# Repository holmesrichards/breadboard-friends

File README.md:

breadboard-friends
==================

A collection of cute breakout boards riding solderless breadboards, mostly for analog audio works

Forked from pichenettes' version and identical except:
- Eagle brd and sch files converted to XML (making possible import into KiCad)
- KiCad versions of boards and schematics
- Added Thonkiconn version of eurojacks

These PCB layouts and schematics are released under a Creative Commons cc-by-sa
3.0 license.

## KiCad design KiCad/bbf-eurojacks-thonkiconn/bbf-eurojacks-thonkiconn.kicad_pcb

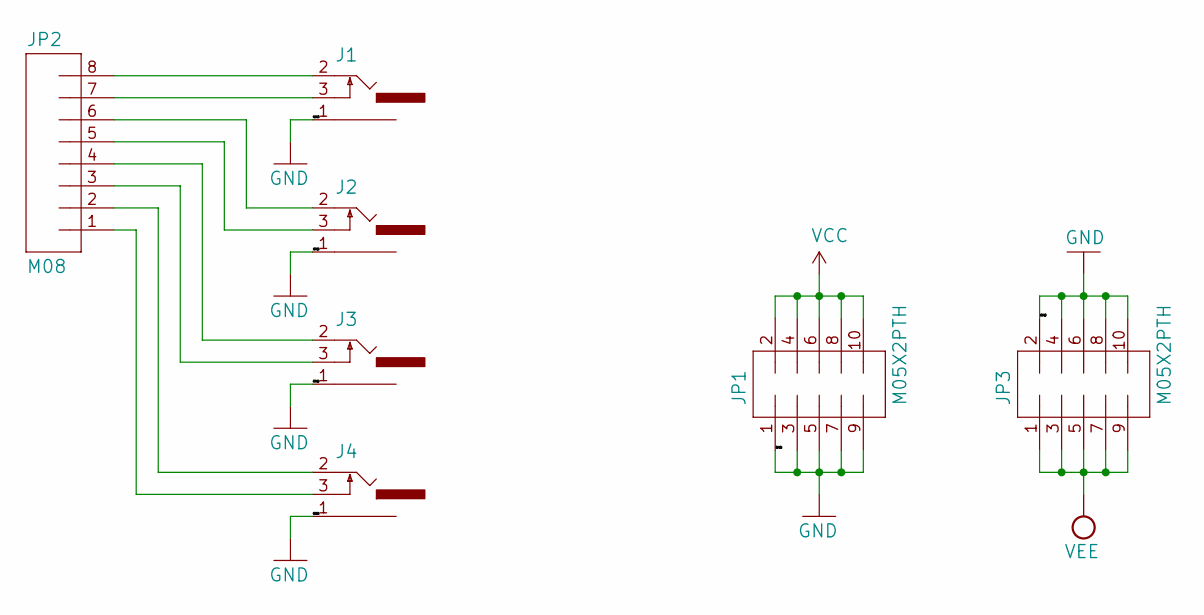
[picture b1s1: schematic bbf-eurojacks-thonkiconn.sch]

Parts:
J1, J2, J3, J4: 1502_03SLOTTED; 3.5mm_tip_switch_thonkiconn
JP1, JP3: M05X2PTH; AVR_ICSP
JP2: M08; 1X08

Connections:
GND: J1.1, J2.1, J3.1, J4.1, JP1.1, JP1.3, JP1.5, JP1.7, JP1.9, JP3.2, JP3.4, JP3.6, JP3.8, JP3.10
unnamed: J1.2, JP2.8
unnamed: J1.3, JP2.7
unnamed: J2.2, JP2.6
unnamed: J2.3, JP2.5
unnamed: J3.2, JP2.4
unnamed: J3.3, JP2.3
unnamed: J4.2, JP2.2
unnamed: J4.3, JP2.1
VCC: JP1.2, JP1.4, JP1.6, JP1.8, JP1.10
VEE: JP3.1, JP3.3, JP3.5, JP3.7, JP3.9

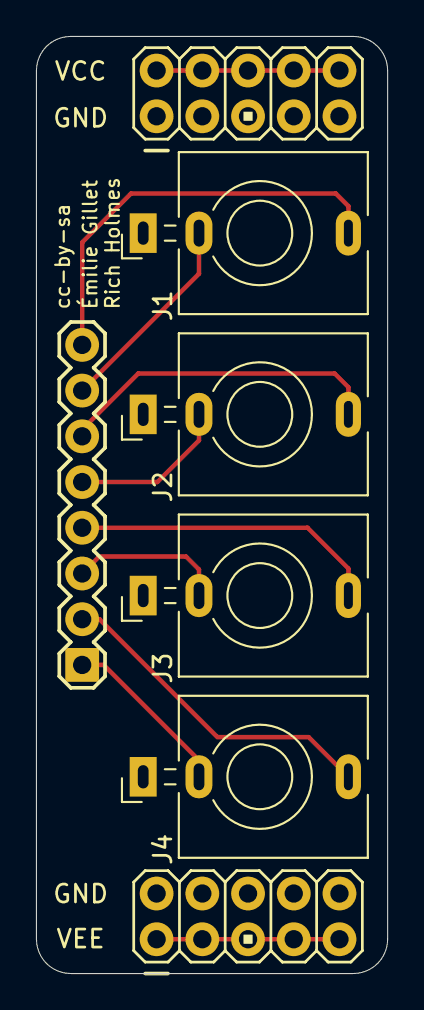
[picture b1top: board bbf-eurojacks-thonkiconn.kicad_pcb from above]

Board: 2 copper layers, 19.5 x 52.1 mm, 7 parts (0 on the bottom side), 11 nets.

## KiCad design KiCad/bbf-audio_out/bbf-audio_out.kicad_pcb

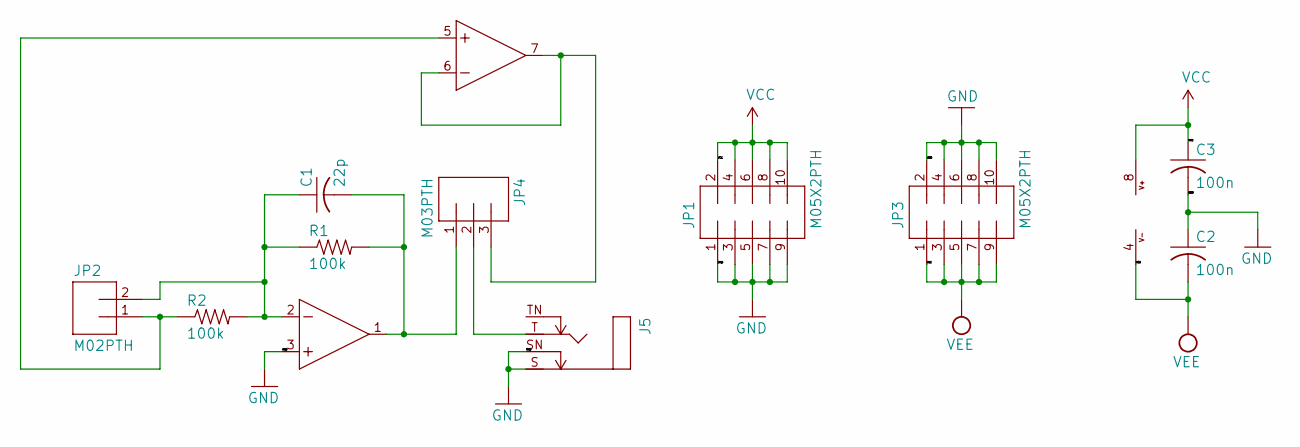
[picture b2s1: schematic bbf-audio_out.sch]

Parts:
C1: 22p; C025-025X050
C2, C3: 100n; C025-025X050
IC1: TL072P; DIL08
J5: MONOSWSLIM; NRJ4HF
JP1, JP3: M05X2PTH; AVR_ICSP
JP2: M02PTH; 1X02
JP4: M03PTH; 1X03
R1, R2: 100k; 0204_7

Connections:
GND: C2.1, C3.2, IC1.3 (+IN), J5.S, J5.SN, JP1.1, JP1.3, JP1.5, JP1.7, JP1.9, JP3.2, JP3.4, JP3.6, JP3.8, JP3.10
unnamed: C1.1, IC1.2 (-IN), JP2.2, R1.1, R2.2
unnamed: C1.2, IC1.1 (OUT), JP4.1, R1.2
unnamed: IC1.5 (+IN), JP2.1, R2.1
unnamed: IC1.6 (-IN), IC1.7 (OUT), JP4.3
unnamed: J5.T, JP4.2
VCC: C3.1, IC1.8 (V+), JP1.2, JP1.4, JP1.6, JP1.8, JP1.10
VEE: C2.2, IC1.4 (V-), JP3.1, JP3.3, JP3.5, JP3.7, JP3.9

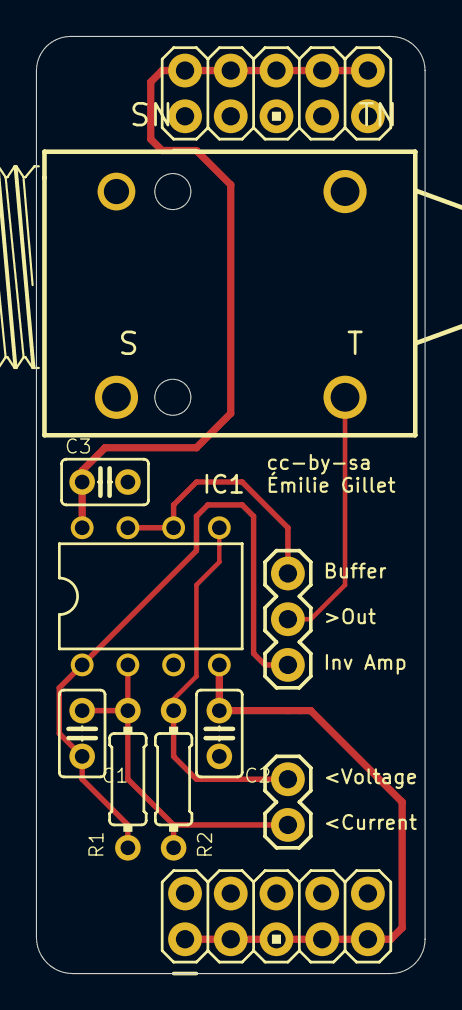
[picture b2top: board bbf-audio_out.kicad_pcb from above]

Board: 2 copper layers, 21.6 x 52.1 mm, 11 parts (0 on the bottom side), 8 nets.

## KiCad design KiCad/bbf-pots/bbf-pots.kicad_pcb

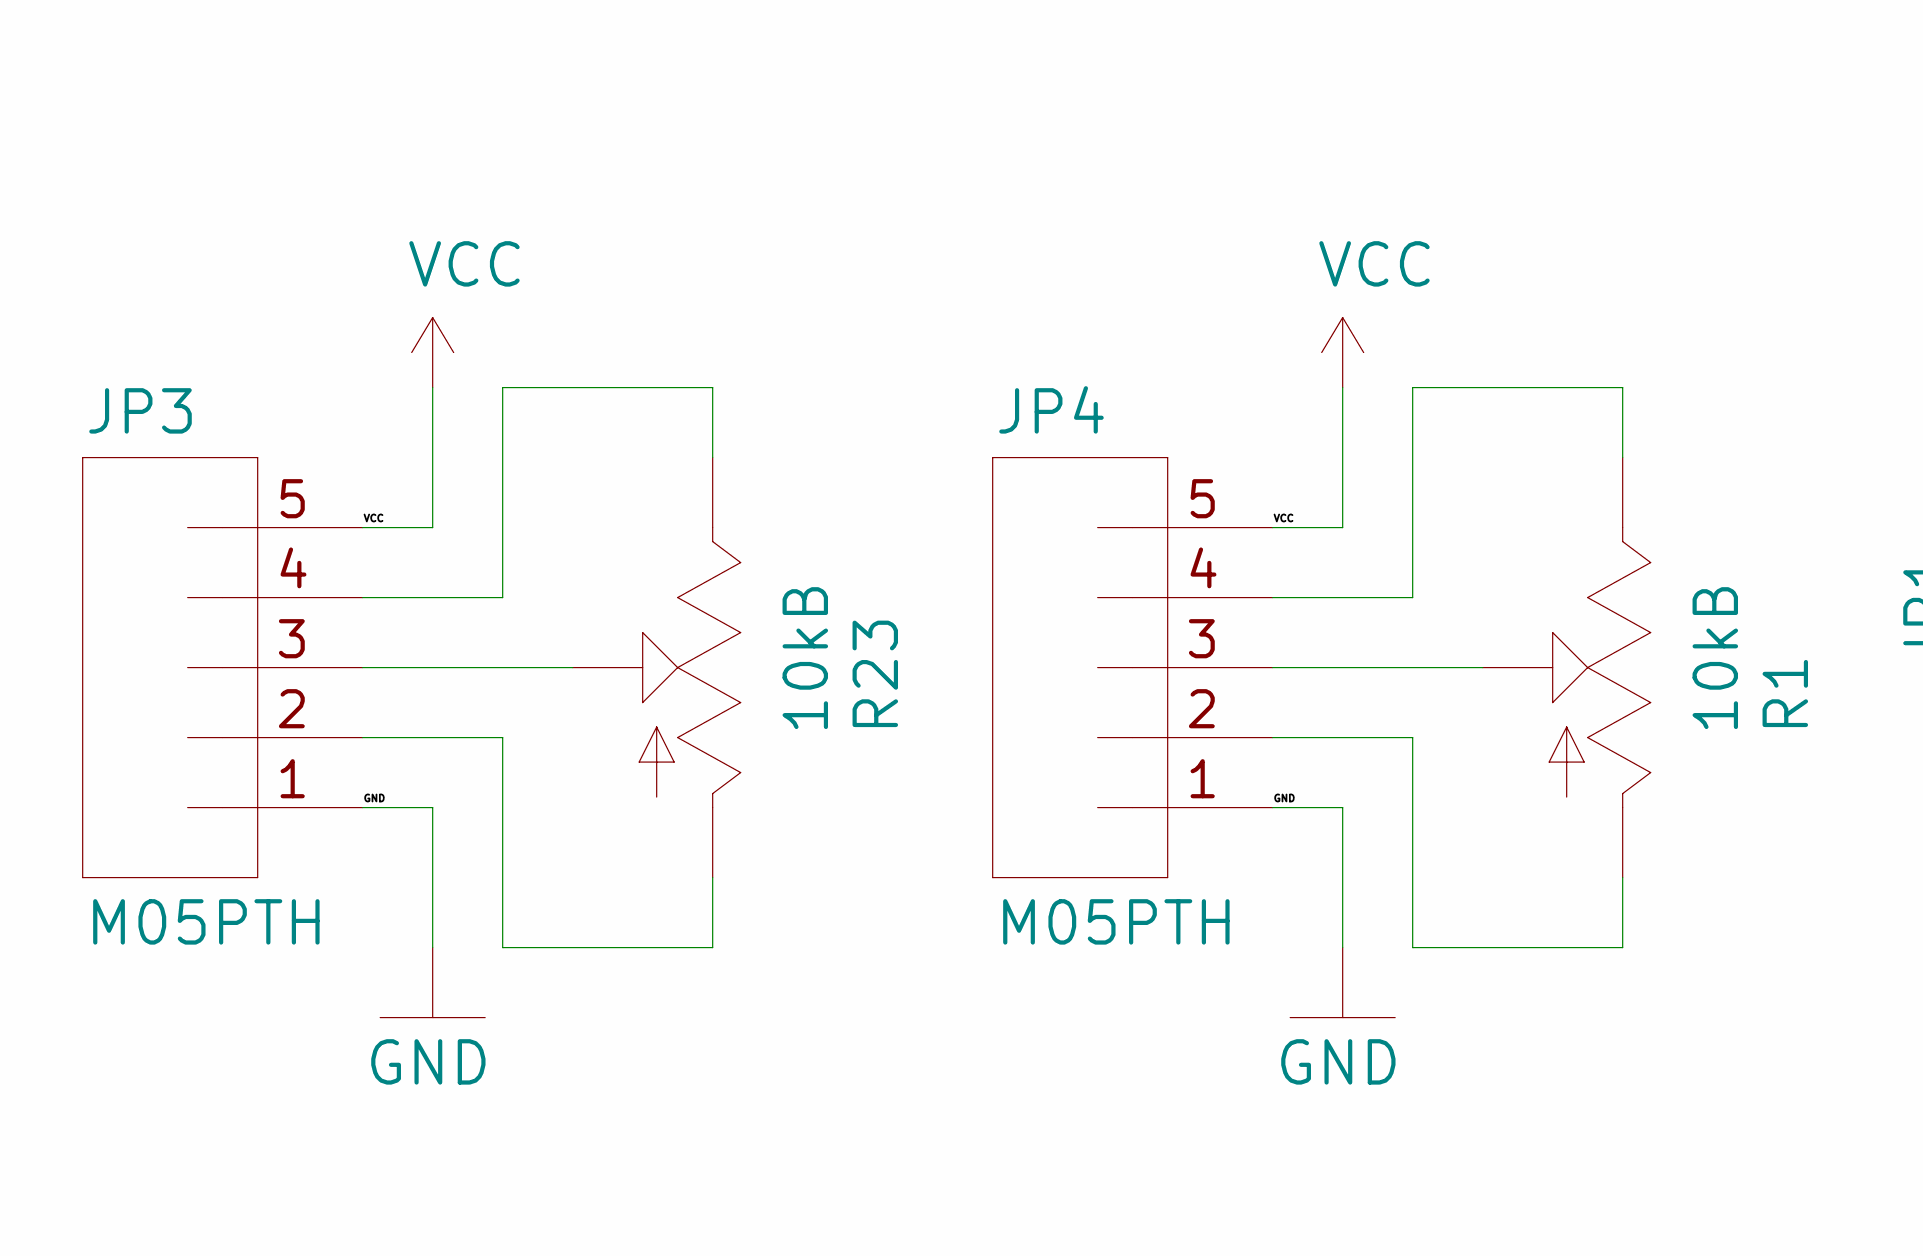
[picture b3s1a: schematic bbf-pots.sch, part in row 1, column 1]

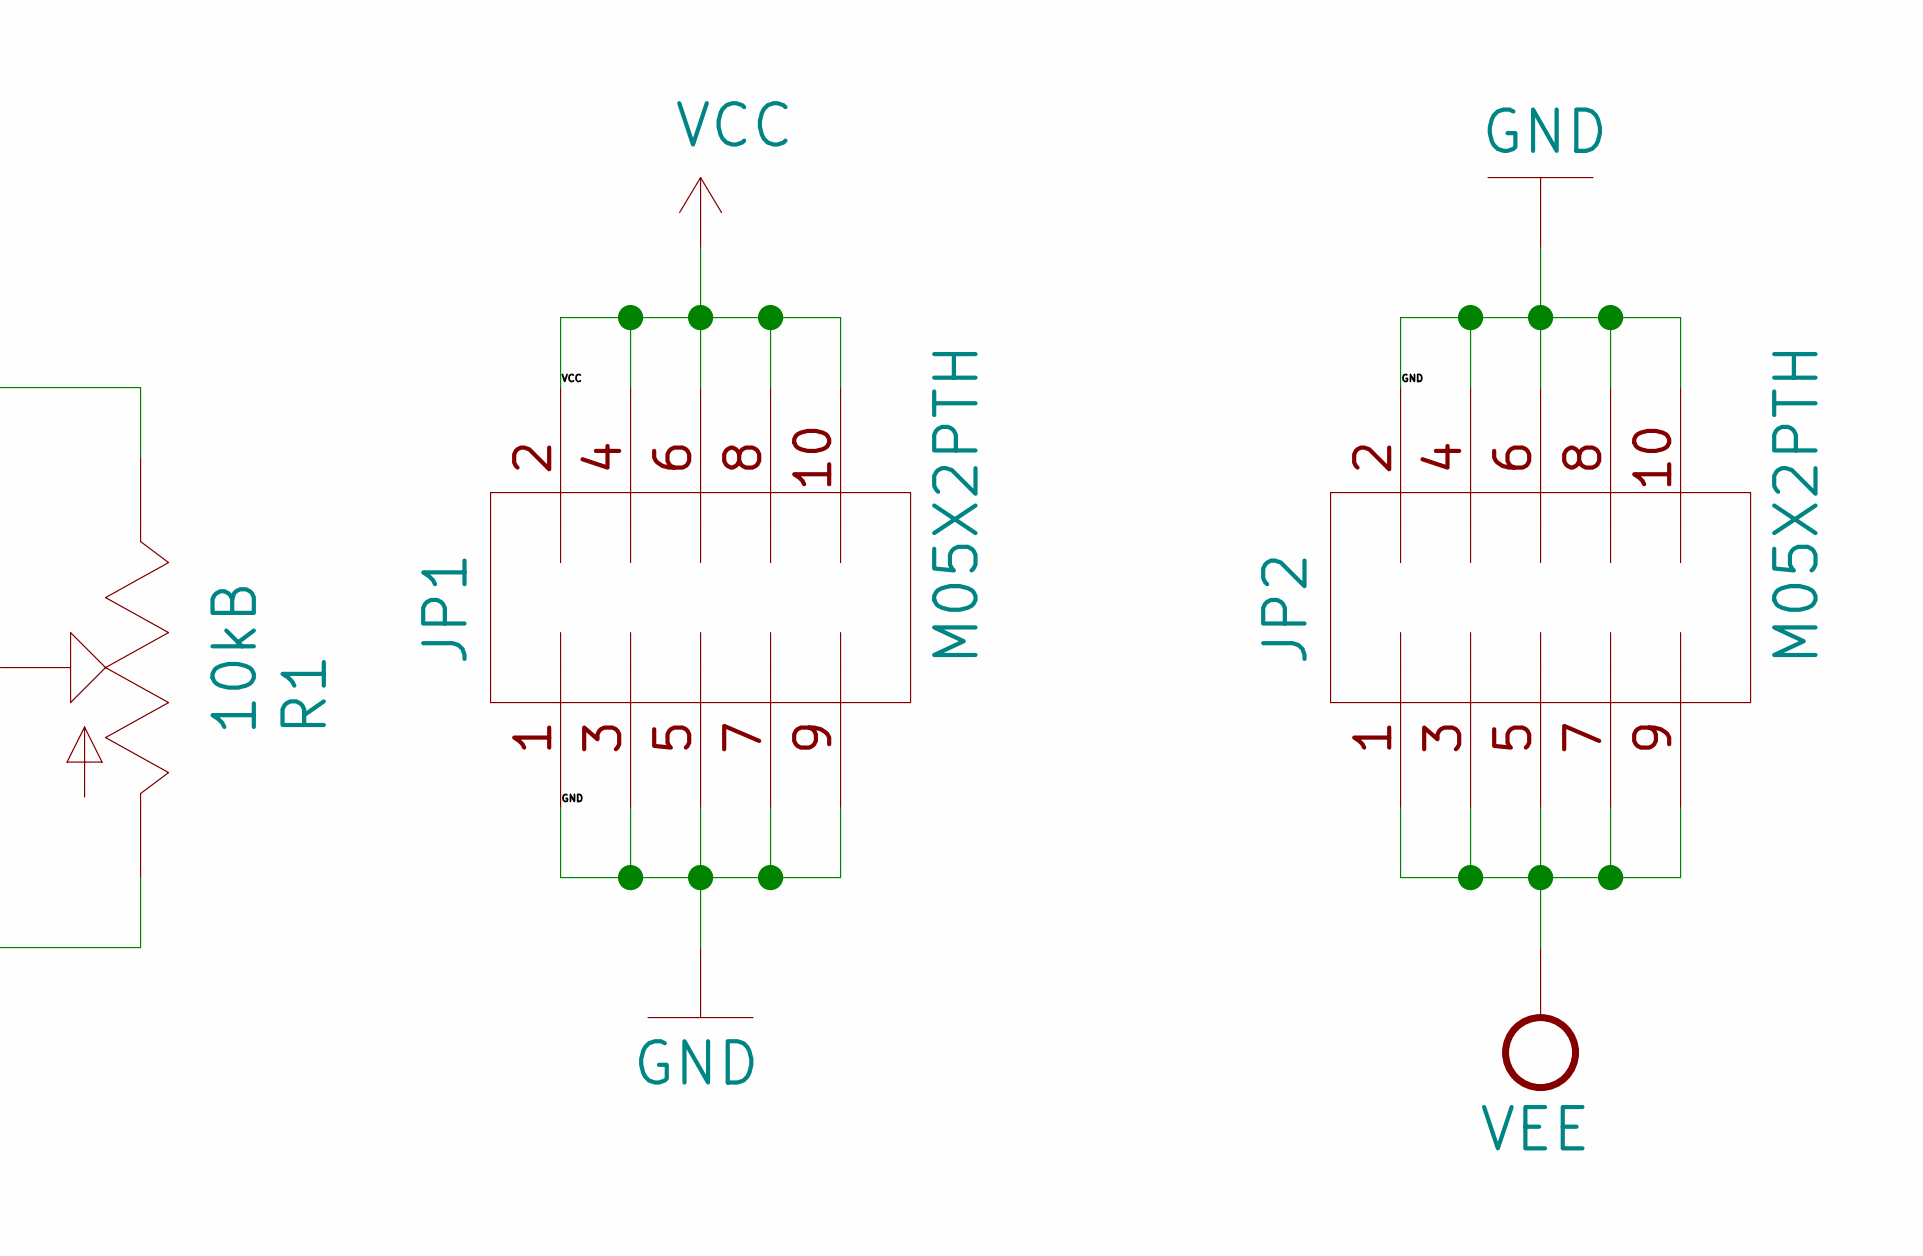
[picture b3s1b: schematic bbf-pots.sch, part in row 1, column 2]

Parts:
JP1, JP2: M05X2PTH; AVR_ICSP
JP3, JP4: M05PTH; 1X05
R1, R23: 10kB; ALPS_POT_VERTICAL

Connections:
GND: JP1.1, JP1.3, JP1.5, JP1.7, JP1.9, JP2.2, JP2.4, JP2.6, JP2.8, JP2.10, JP3.1, JP4.1
unnamed: JP3.2, R23.P$3 (A)
unnamed: JP3.3, R23.P$2 (S)
unnamed: JP3.4, R23.P$1 (E)
unnamed: JP4.2, R1.P$3 (A)
unnamed: JP4.3, R1.P$2 (S)
unnamed: JP4.4, R1.P$1 (E)
VCC: JP1.2, JP1.4, JP1.6, JP1.8, JP1.10, JP3.5, JP4.5
VEE: JP2.1, JP2.3, JP2.5, JP2.7, JP2.9

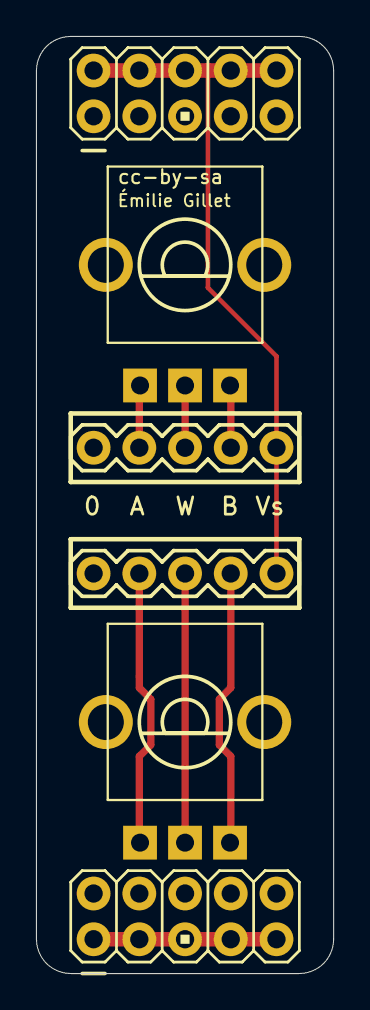
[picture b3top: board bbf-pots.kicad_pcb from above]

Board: 2 copper layers, 16.5 x 52.1 mm, 6 parts (0 on the bottom side), 9 nets.

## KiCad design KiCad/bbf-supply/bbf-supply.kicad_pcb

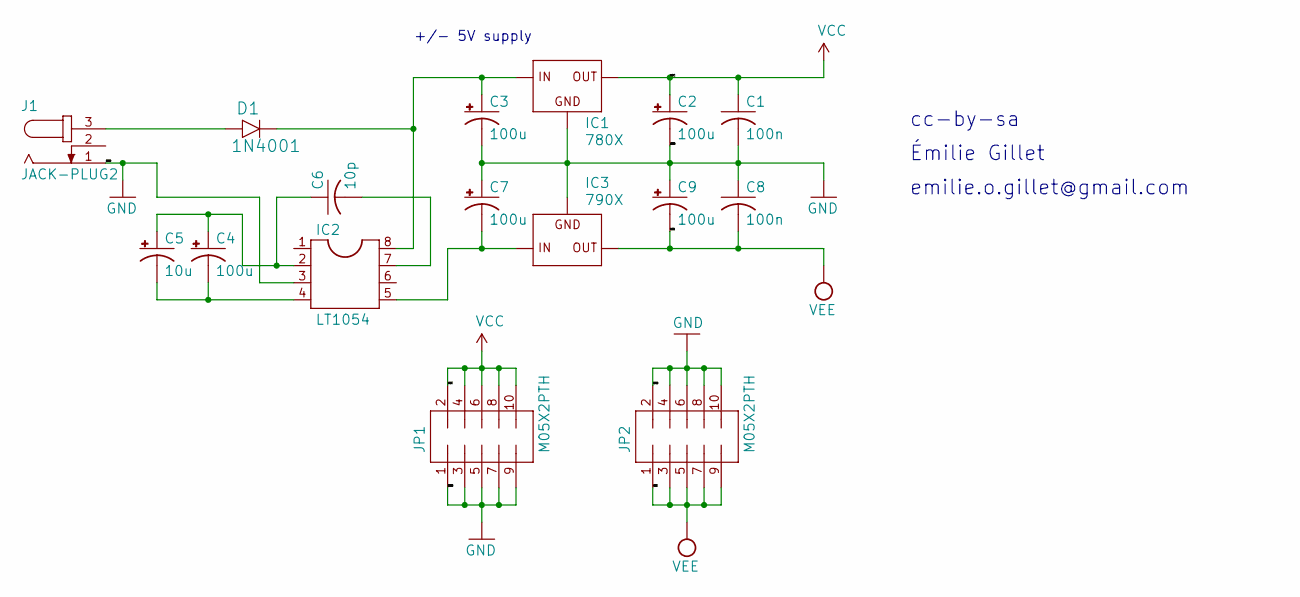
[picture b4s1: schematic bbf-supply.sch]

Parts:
C1, C8: 100n; C025-025X050
C2, C3, C7, C9: 100u; E2,5-7
C4: 100u; E2,5-6
C5: 10u; E2,5-5
C6: 10p; C025-025X050
D1: 1N4001; DO41-3
IC1: 780X; 78XXS
IC2: LT1054; DIL08
IC3: 790X; 79XXS
J1: JACK-PLUG2; SPC4078_BIG_HOLES
JP1, JP2: M05X2PTH; AVR_ICSP

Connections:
GND: C1.2, C2.-, C3.-, C7.+, C8.1, C9.+, IC1.GND, IC2.3, IC3.GND, J1.1, JP1.1, JP1.3, JP1.5, JP1.7, JP1.9, JP2.2, JP2.4, JP2.6, JP2.8, JP2.10
unnamed: C3.+, D1.C, IC1.IN, IC2.8
unnamed: C4.+, C5.+, C6.1, IC2.2
unnamed: C4.-, C5.-, IC2.4
unnamed: C6.2, IC2.7
unnamed: C7.-, IC2.5, IC3.IN
unnamed: D1.A, J1.3
VCC: C1.1, C2.+, IC1.OUT, JP1.2, JP1.4, JP1.6, JP1.8, JP1.10
VEE: C8.2, C9.-, IC3.OUT, JP2.1, JP2.3, JP2.5, JP2.7, JP2.9

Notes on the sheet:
cc-by-sa
Émilie Gillet
emilie.o.gillet@gmail.com
+/- 5V supply

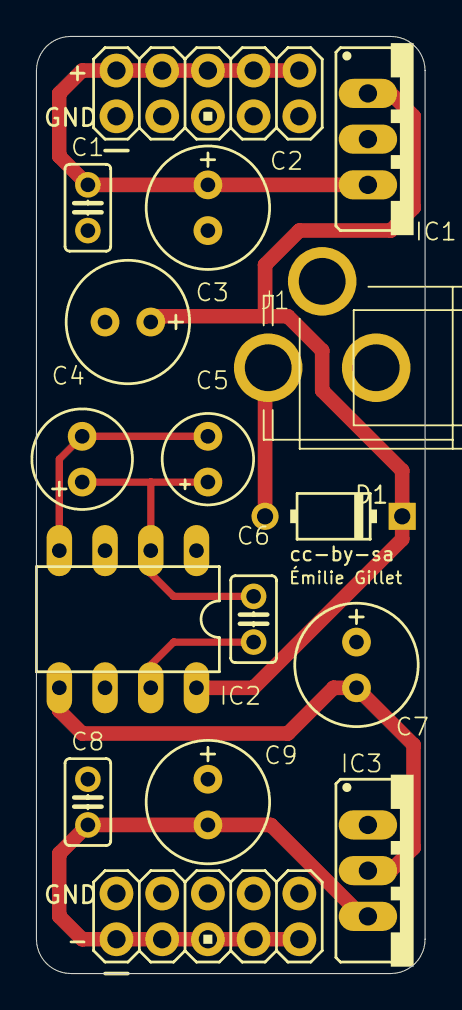
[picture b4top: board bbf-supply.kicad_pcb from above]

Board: 2 copper layers, 21.6 x 52.1 mm, 16 parts (0 on the bottom side), 9 nets.

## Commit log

2020-03-22 add KiCad stuff
2020-03-22 XML conversions
2020-03-22 KiCad conversions and (KiCad) Thonkiconn version of eurojacks
2020-03-22 lose KiCad cruft
2020-03-23 Updated README for fork
2020-03-23 euroracks-thonkiconn Gerbers
2021-01-17 Include lib table files
